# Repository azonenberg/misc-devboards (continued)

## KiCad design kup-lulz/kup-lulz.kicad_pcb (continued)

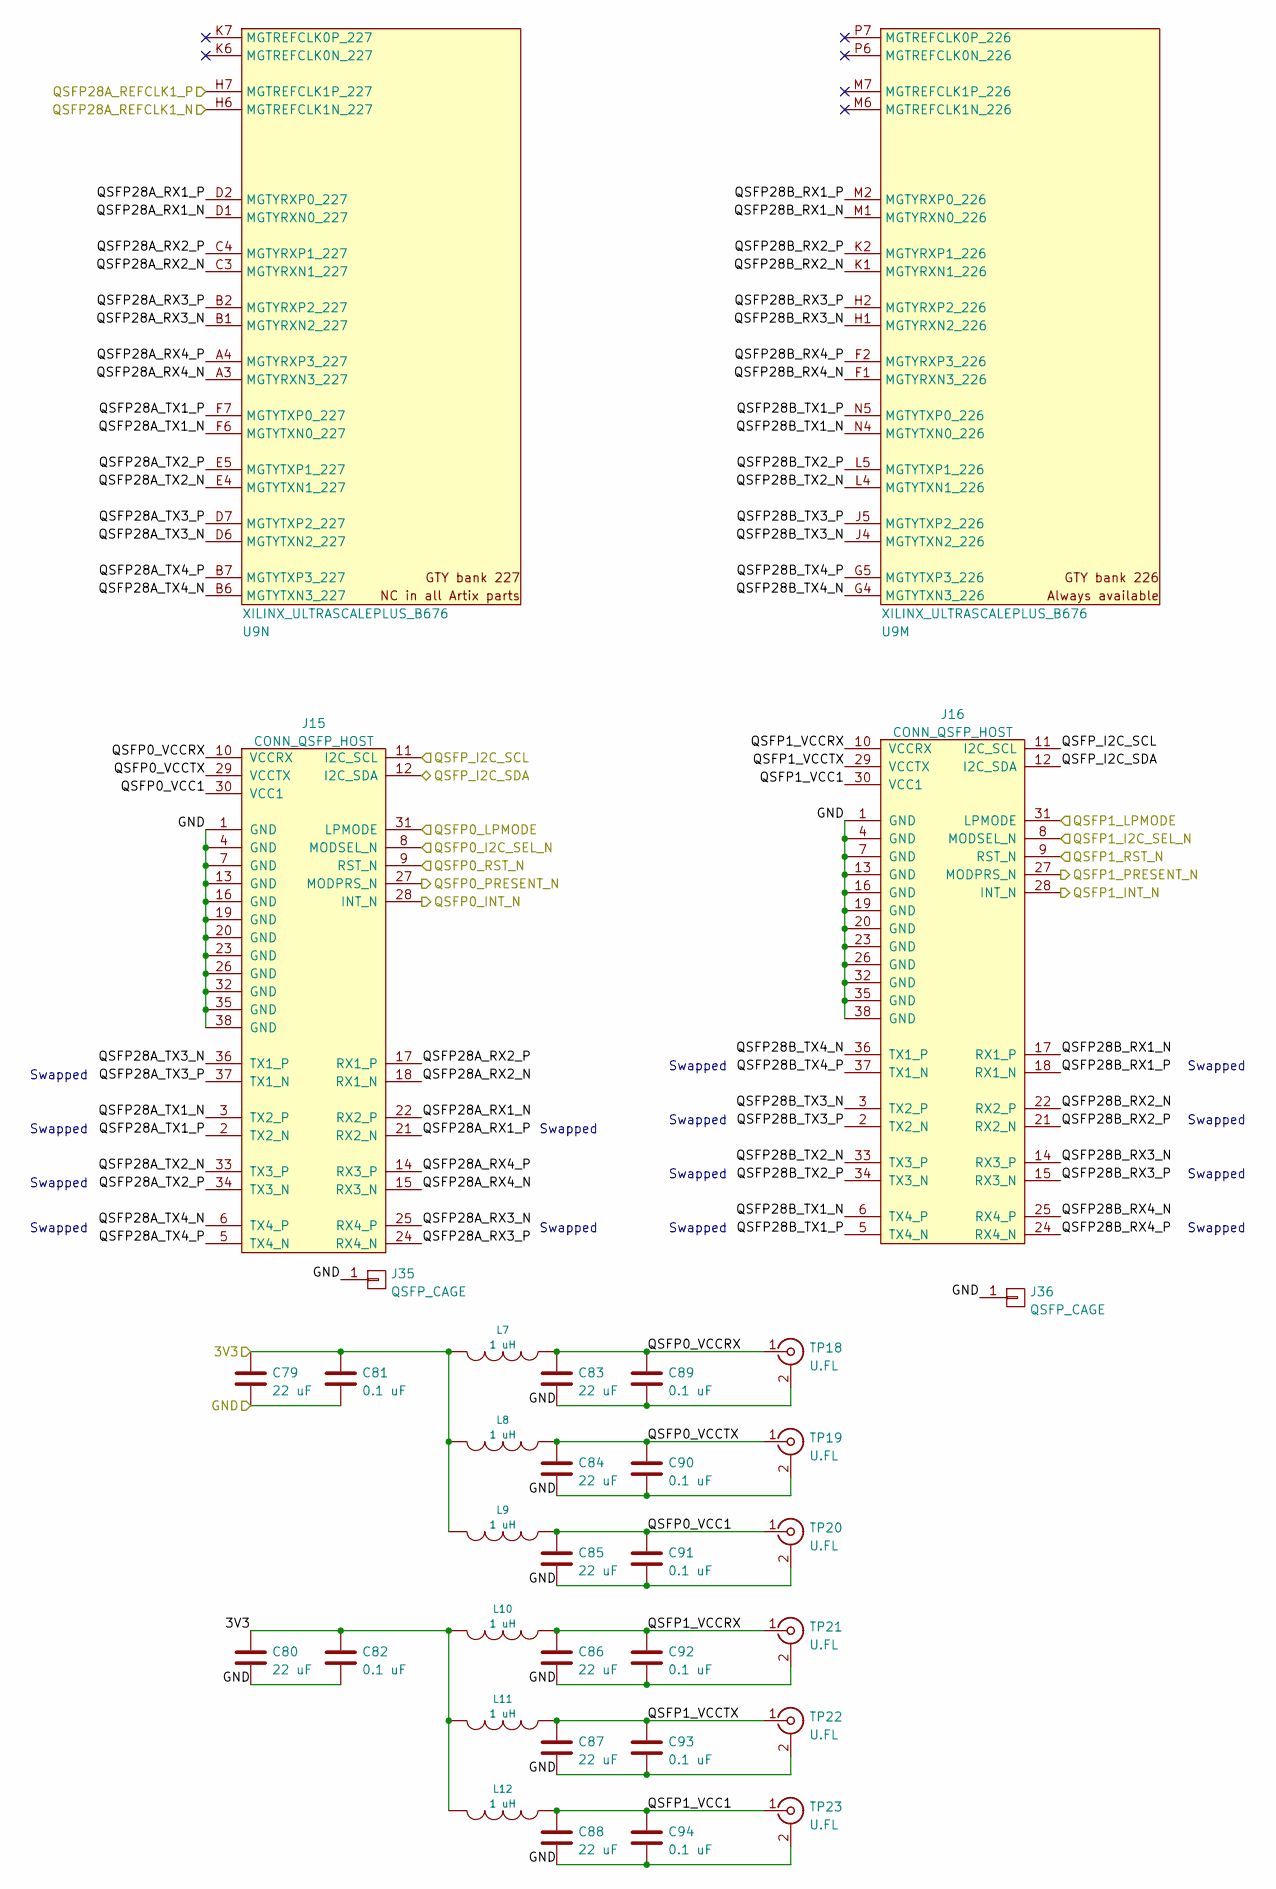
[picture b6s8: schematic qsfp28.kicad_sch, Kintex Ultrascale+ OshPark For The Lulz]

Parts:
C79, C80, C83, C84, C85, C86, C87, C88: 22 uF; EIA_1210_CAP_NOSILK
C81, C82, C89, C90, C91, C92, C93, C94: 0.1 uF; EIA_0402_CAP_NOSILK
J15, J16: CONN_QSFP_HOST; CONN_ZQSFP+_TE_1551920-2
J35, J36: QSFP_CAGE; CONN_ZQSFP+_CAGE_TE_4-2170705-5
L7, L8, L9, L10, L11, L12: 1 uH; EIA_0805_INDUCTOR_NOSILK
TP18, TP19, TP20, TP21, TP22, TP23: U.FL; CONN_U.FL_TE_1909763-1
U9: XILINX_ULTRASCALEPLUS_B676; BGA_676_27x27_FULLARRAY_1MM_FFG676

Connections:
/3V3: C79.1, C80.1, C81.1, C82.1, L7.2, L8.2, L9.2, L10.2, L11.2, L12.2; also elsewhere on the board
/GND: C79.2, C80.2, C81.2, C82.2, C83.2, C84.2, C85.2, C86.2, C87.2, C88.2, C89.2, C90.2, C91.2, C92.2, C93.2, C94.2, J15.1 (GND), J15.4 (GND), J15.7 (GND), J15.13 (GND), J15.16 (GND), J15.19 (GND), J15.20 (GND), J15.23 (GND), J15.26 (GND), J15.32 (GND), J15.35 (GND), J15.38 (GND), J16.1 (GND), J16.4 (GND), J16.7 (GND), J16.13 (GND), J16.16 (GND), J16.19 (GND), J16.20 (GND), J16.23 (GND), J16.26 (GND), J16.32 (GND), J16.35 (GND), J16.38 (GND), J35.1, J36.1, TP18.2 (Ext), TP19.2 (Ext), TP20.2 (Ext), TP21.2 (Ext), TP22.2 (Ext), TP23.2 (Ext); also elsewhere on the board
/Management/QSFP0_I2C_SEL_N: J15.8 (MODSEL_N); also elsewhere on the board
/Management/QSFP0_INT_N: J15.28 (INT_N); also elsewhere on the board
/Management/QSFP0_LPMODE: J15.31 (LPMODE); also elsewhere on the board
/Management/QSFP0_PRESENT_N: J15.27 (MODPRS_N); also elsewhere on the board
/Management/QSFP0_RST_N: J15.9 (RST_N); also elsewhere on the board
/Management/QSFP1_I2C_SEL_N: J16.8 (MODSEL_N); also elsewhere on the board
/Management/QSFP1_INT_N: J16.28 (INT_N); also elsewhere on the board
/Management/QSFP1_LPMODE: J16.31 (LPMODE); also elsewhere on the board
/Management/QSFP1_PRESENT_N: J16.27 (MODPRS_N); also elsewhere on the board
/Management/QSFP1_RST_N: J16.9 (RST_N); also elsewhere on the board
/Management/QSFP_I2C_SCL: J15.11 (I2C_SCL), J16.11 (I2C_SCL); also elsewhere on the board
/Management/QSFP_I2C_SDA: J15.12 (I2C_SDA), J16.12 (I2C_SDA); also elsewhere on the board
/QSFP28 interface/QSFP0_VCC1: C85.1, C91.1, J15.30 (VCC1), L9.1, TP20.1 (In)
/QSFP28 interface/QSFP0_VCCRX: C83.1, C89.1, J15.10 (VCCRX), L7.1, TP18.1 (In)
/QSFP28 interface/QSFP0_VCCTX: C84.1, C90.1, J15.29 (VCCTX), L8.1, TP19.1 (In)
/QSFP28 interface/QSFP1_VCC1: C88.1, C94.1, J16.30 (VCC1), L12.1, TP23.1 (In)
/QSFP28 interface/QSFP1_VCCRX: C86.1, C92.1, J16.10 (VCCRX), L10.1, TP21.1 (In)
/QSFP28 interface/QSFP1_VCCTX: C87.1, C93.1, J16.29 (VCCTX), L11.1, TP22.1 (In)
/QSFP28 interface/QSFP28A_RX1_N: J15.22 (RX2_P), U9.D1 (MGTYRXN0_227)
/QSFP28 interface/QSFP28A_RX1_P: J15.21 (RX2_N), U9.D2 (MGTYRXP0_227)
/QSFP28 interface/QSFP28A_RX2_N: J15.18 (RX1_N), U9.C3 (MGTYRXN1_227)
/QSFP28 interface/QSFP28A_RX2_P: J15.17 (RX1_P), U9.C4 (MGTYRXP1_227)
/QSFP28 interface/QSFP28A_RX3_N: J15.25 (RX4_P), U9.B1 (MGTYRXN2_227)
/QSFP28 interface/QSFP28A_RX3_P: J15.24 (RX4_N), U9.B2 (MGTYRXP2_227)
/QSFP28 interface/QSFP28A_RX4_N: J15.15 (RX3_N), U9.A3 (MGTYRXN3_227)
/QSFP28 interface/QSFP28A_RX4_P: J15.14 (RX3_P), U9.A4 (MGTYRXP3_227)
/QSFP28 interface/QSFP28A_TX1_N: J15.3 (TX2_P), U9.F6 (MGTYTXN0_227)
/QSFP28 interface/QSFP28A_TX1_P: J15.2 (TX2_N), U9.F7 (MGTYTXP0_227)
/QSFP28 interface/QSFP28A_TX2_N: J15.33 (TX3_P), U9.E4 (MGTYTXN1_227)
/QSFP28 interface/QSFP28A_TX2_P: J15.34 (TX3_N), U9.E5 (MGTYTXP1_227)
/QSFP28 interface/QSFP28A_TX3_N: J15.36 (TX1_P), U9.D6 (MGTYTXN2_227)
/QSFP28 interface/QSFP28A_TX3_P: J15.37 (TX1_N), U9.D7 (MGTYTXP2_227)
/QSFP28 interface/QSFP28A_TX4_N: J15.6 (TX4_P), U9.B6 (MGTYTXN3_227)
/QSFP28 interface/QSFP28A_TX4_P: J15.5 (TX4_N), U9.B7 (MGTYTXP3_227)
/QSFP28 interface/QSFP28B_RX1_N: J16.17 (RX1_P), U9.M1 (MGTYRXN0_226)
/QSFP28 interface/QSFP28B_RX1_P: J16.18 (RX1_N), U9.M2 (MGTYRXP0_226)
/QSFP28 interface/QSFP28B_RX2_N: J16.22 (RX2_P), U9.K1 (MGTYRXN1_226)
/QSFP28 interface/QSFP28B_RX2_P: J16.21 (RX2_N), U9.K2 (MGTYRXP1_226)
/QSFP28 interface/QSFP28B_RX3_N: J16.14 (RX3_P), U9.H1 (MGTYRXN2_226)
/QSFP28 interface/QSFP28B_RX3_P: J16.15 (RX3_N), U9.H2 (MGTYRXP2_226)
/QSFP28 interface/QSFP28B_RX4_N: J16.25 (RX4_P), U9.F1 (MGTYRXN3_226)
/QSFP28 interface/QSFP28B_RX4_P: J16.24 (RX4_N), U9.F2 (MGTYRXP3_226)
/QSFP28 interface/QSFP28B_TX1_N: J16.6 (TX4_P), U9.N4 (MGTYTXN0_226)
/QSFP28 interface/QSFP28B_TX1_P: J16.5 (TX4_N), U9.N5 (MGTYTXP0_226)
/QSFP28 interface/QSFP28B_TX2_N: J16.33 (TX3_P), U9.L4 (MGTYTXN1_226)
/QSFP28 interface/QSFP28B_TX2_P: J16.34 (TX3_N), U9.L5 (MGTYTXP1_226)
/QSFP28 interface/QSFP28B_TX3_N: J16.3 (TX2_P), U9.J4 (MGTYTXN2_226)
/QSFP28 interface/QSFP28B_TX3_P: J16.2 (TX2_N), U9.J5 (MGTYTXP2_226)
/QSFP28 interface/QSFP28B_TX4_N: J16.36 (TX1_P), U9.G4 (MGTYTXN3_226)
/QSFP28 interface/QSFP28B_TX4_P: J16.37 (TX1_N), U9.G5 (MGTYTXP3_226)
/REFCLK2_N: U9.H6 (MGTREFCLK1N_227); also elsewhere on the board
/REFCLK2_P: U9.H7 (MGTREFCLK1P_227); also elsewhere on the board

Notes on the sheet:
Swapped

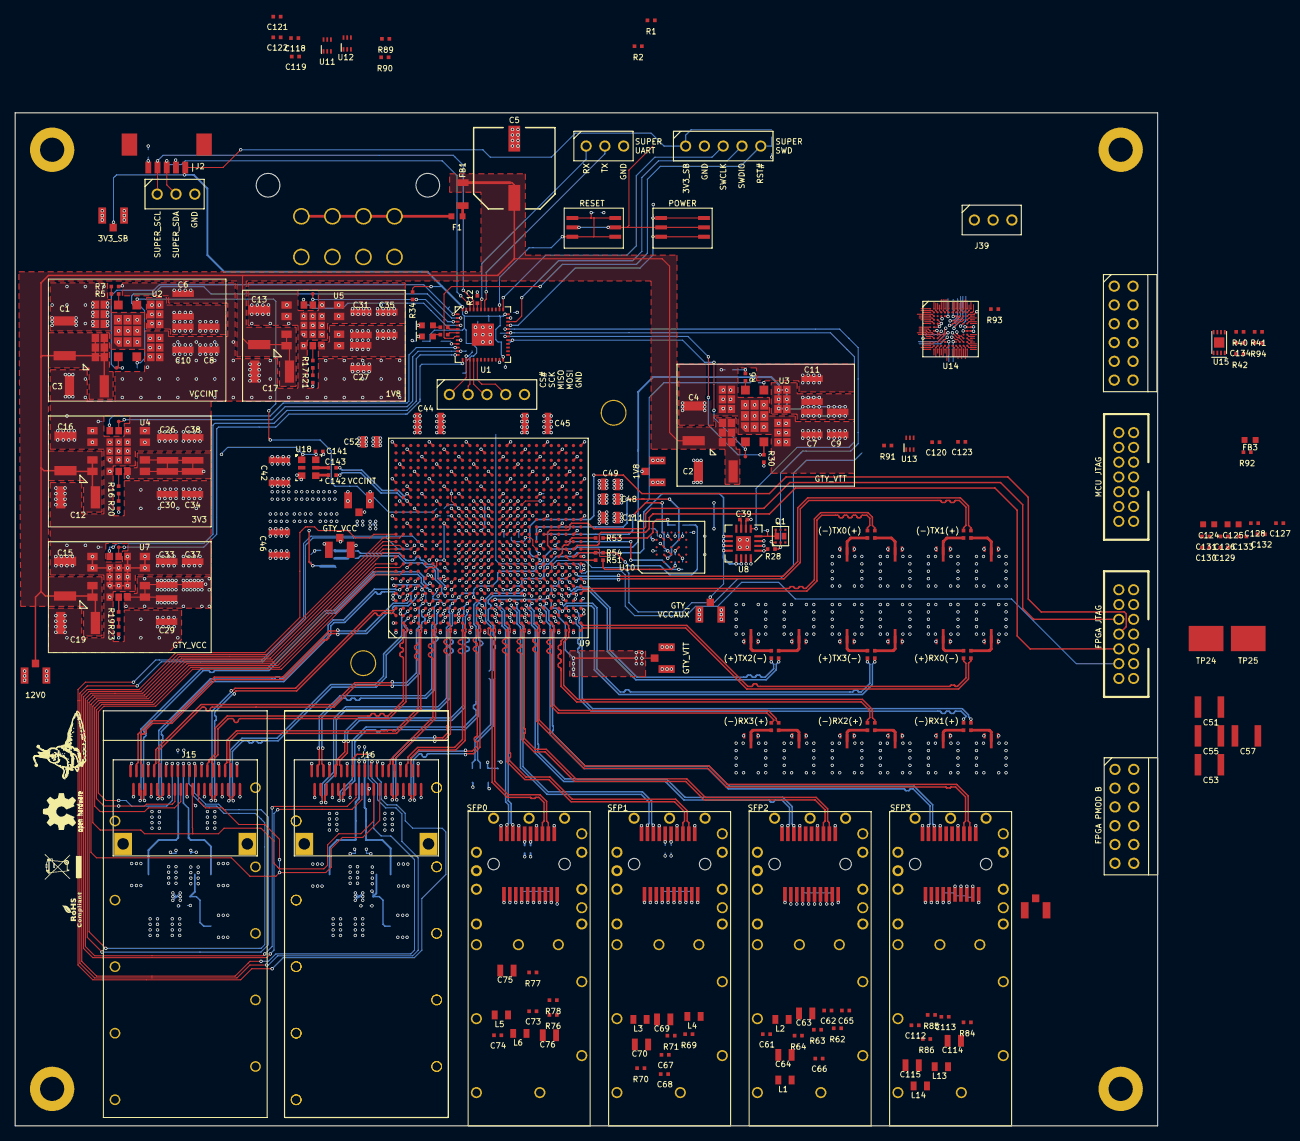
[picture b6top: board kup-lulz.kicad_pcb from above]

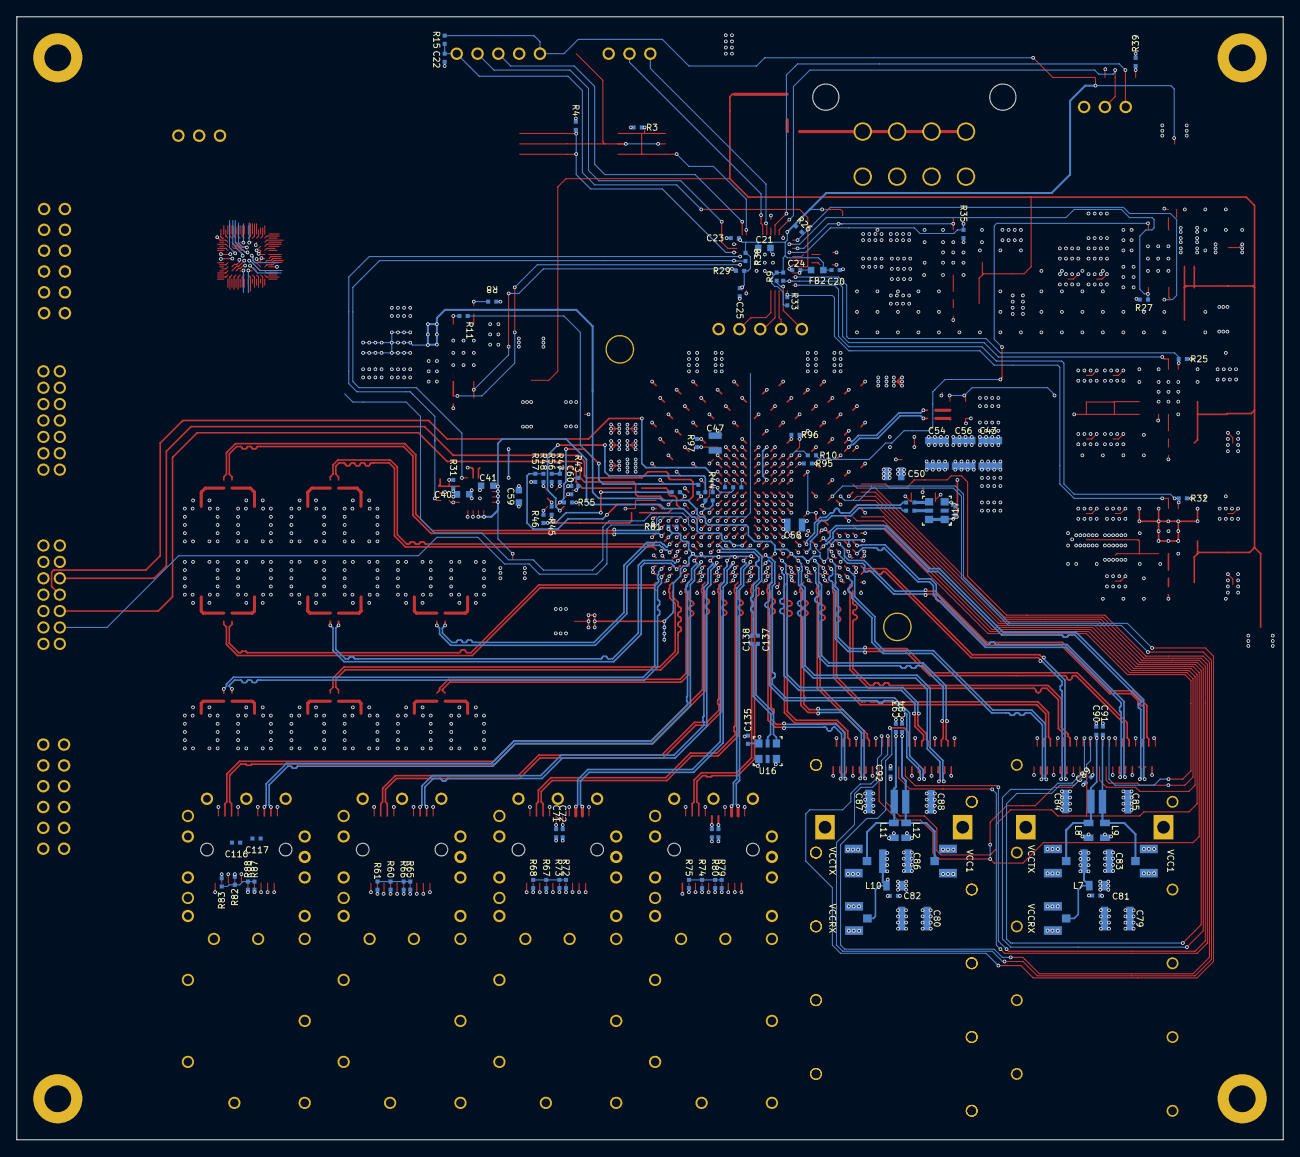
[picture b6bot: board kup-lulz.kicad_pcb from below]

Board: 4 copper layers, 154.5 x 137.0 mm, 340 parts (110 on the bottom side), 286 nets.

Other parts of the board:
J36#2: QSFP_CAGE; CONN_ZQSFP+_CAGE_TE_4-2170705-5

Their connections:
/GND: J36#2.1; also elsewhere on the board

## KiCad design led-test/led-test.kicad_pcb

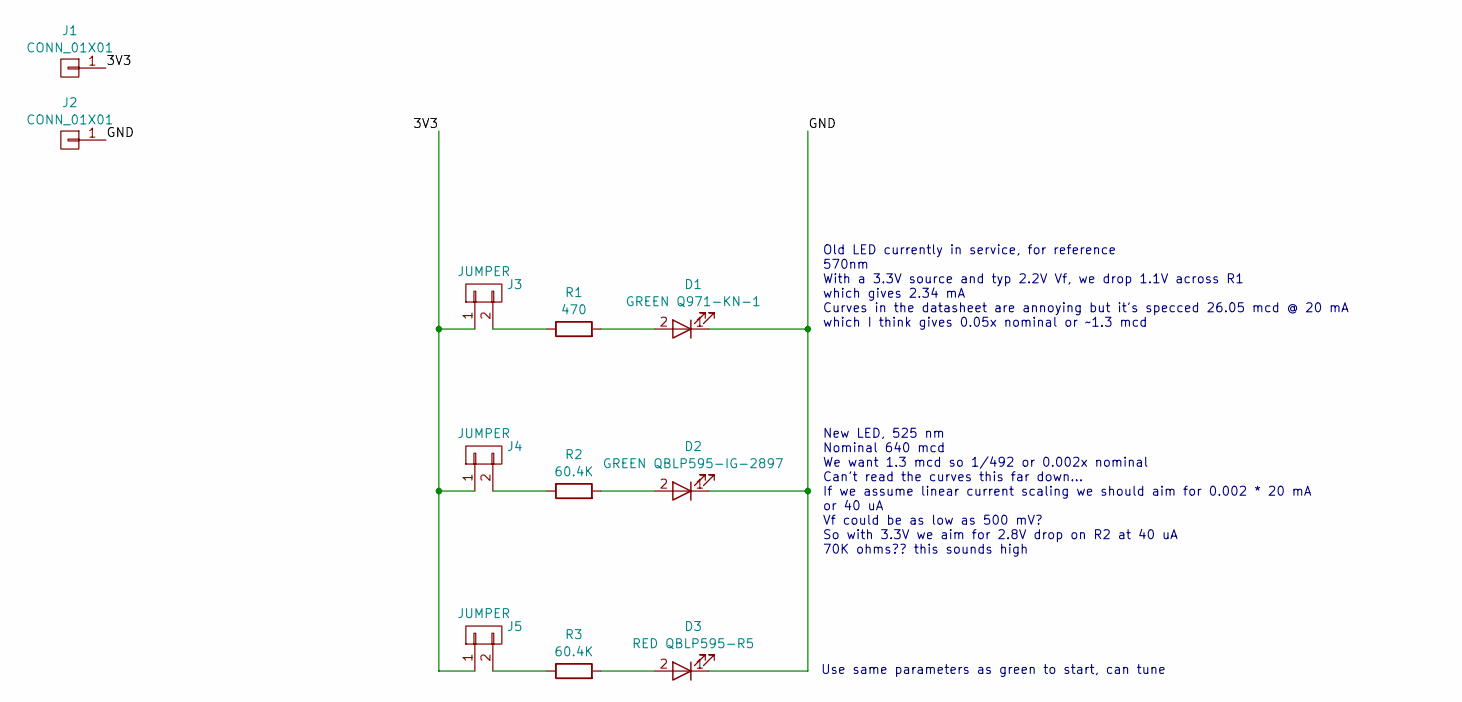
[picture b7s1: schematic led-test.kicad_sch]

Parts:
D1: GREEN Q971-KN-1; EIA_0603_LED
D2: GREEN QBLP595-IG-2897; EIA_0402_LED
D3: RED QBLP595-R5; EIA_0402_LED
J1, J2: CONN_01X01; TESTPOINT_SMT_KEYSTONE_5016
J3, J4, J5: JUMPER; CONN_HEADER_2.54MM_1x2
R1: 470; EIA_0402_RES_NOSILK
R2, R3: 60.4K; EIA_0402_RES_NOSILK

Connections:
/3V3: J1.1, J3.1, J4.1, J5.1
/GND: D1.1 (K), D2.1 (K), D3.1 (K), J2.1
unnamed: D1.2 (A), R1.2
unnamed: D2.2 (A), R2.2
unnamed: D3.2 (A), R3.2
unnamed: J3.2, R1.1
unnamed: J4.2, R2.1
unnamed: J5.2, R3.1

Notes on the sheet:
Old LED currently in service, for reference 570nm With a 3.3V source and typ 2.2V Vf, we drop 1.1V across R1 which gives 2.34 mA Curves in the datasheet are annoying but it's specced 26.05 mcd @ 20 mA which I think gives 0.05x nominal or ~1.3 mcd
New LED, 525 nm Nominal 640 mcd We want 1.3 mcd so 1/492 or 0.002x nominal Can't read the curves this far down... If we assume linear current scaling we should aim for 0.002 * 20 mA or 40 uA Vf could be as low as 500 mV? So with 3.3V we aim for 2.8V drop on R2 at 40 uA 70K ohms?? this sounds high
Use same parameters as green to start, can tune

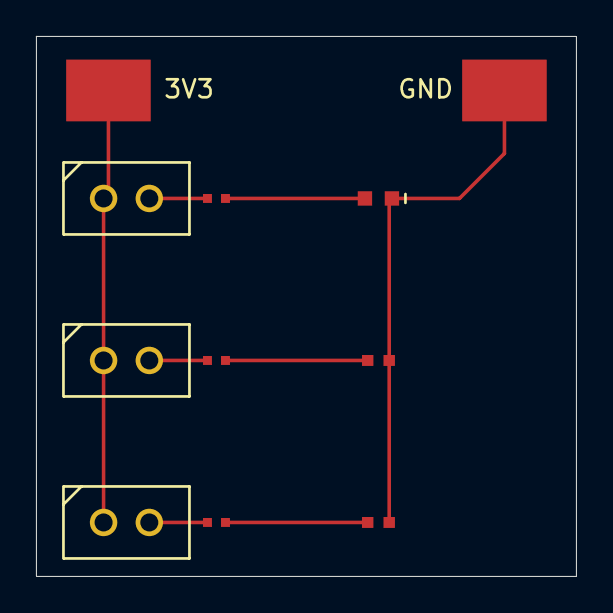
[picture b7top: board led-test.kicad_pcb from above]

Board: 2 copper layers, 30.0 x 30.0 mm, 11 parts (0 on the bottom side), 8 nets.

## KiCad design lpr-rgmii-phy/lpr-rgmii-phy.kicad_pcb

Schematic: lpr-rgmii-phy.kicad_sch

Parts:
C1, C4: 22 uF; EIA_1812_CAP_NOSILK
C2, C3, C5, C6: 22 uF; EIA_1210_CAP_NOSILK
C7, C17, C18, C23, C24, C25, C26, C27, C28, C29, C30, C31, C32, C33, C34, C35: 0.47 uF; EIA_0402_CAP_NOSILK
C8, C9, C10, C11, C12, C19, C20, C21, C22: 4.7 uF; EIA_0603_CAP_NOSILK
C13, C14, C15, C16: 0.1 uF; EIA_0402_CAP_NOSILK
FB1, FB2, FB3, FB4: MI0603J601R-10; EIA_0603_INDUCTOR_NOSILK
J1: LPR_HEADER; CONN_HEADER_2.0MM_2x20_SMT_MOLEX_0877594014
J2: 0826-1G1T-23-F; CONN_BELFUSE_0826_1G1T_23_F
M1: LOGO; LONGTHING-1200DPI
M2: LOGO; Logo_silk_OSHW_6x6mm
M3: LOGO; Logo_silk_ROHS_5x2.8mm
M4: LOGO; Logo_silk_WEEE_3.4x5mm
R1, R3, R4: 100K; EIA_0402_RES_NOSILK
R2: 22.1K; EIA_0402_RES_NOSILK
R5, R6: 470; EIA_0402_RES_NOSILK
R7, R9, R10, R11, R12, R13, R14: 33; EIA_0402_RES_NOSILK
R8, R16, R24: 1K; EIA_0402_RES_NOSILK
R15: 12.1K 1%; EIA_0402_RES_NOSILK
R17, R18, R19, R20, R21, R22, R23, R25, R26: 10K; EIA_0402_RES_NOSILK
TP1, TP2, TP3, TP4, TP5, TP6: U.FL; CONN_U.FL_TE_1909763-1
TP7, TP9: TESTPOINT; TESTPOINT_SMT_0.5MM
TP8: TESTCLIP; TESTPOINT_SMT_KEYSTONE_5016
U1, U2: MUN12AD03-SE; MODULE_CYNTEC_MUN12AD03-SE
U3: ECS-1612MV-250-CN; OSCILLATOR_1.6x1.2
U4: KSZ9031RN; QFN_48_0.5MM_7x7MM
U5, U6: RCLAMP0514M; SOP_10_0.5MM_3MM

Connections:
/1V2: C5.1, C6.1, C8.1, C11.1, FB1.1, FB3.1, FB4.1, R3.1, TP2.1 (In), U2.4 (VOUT), U2.5 (VOUT)
/1V2_FB: R3.2, R4.1, U2.6 (FB)
/1V2_PGOOD: R26.2, TP7.1, U2.7 (PGOOD)
/3V3: C2.1, C3.1, C7.1, C9.1, C10.1, C17.1, C23.1, C28.1, FB2.1, R1.1, R5.1, R6.1, R17.1, R18.1, R19.1, R20.1, R24.1, TP1.1 (In), U1.4 (VOUT), U1.5 (VOUT), U3.1 (E/D#), U3.4 (Vdd), U4.16 (DVDDH), U4.34 (DVDDH), U4.40 (DVDDH)
/3V3_FB: R1.2, R2.1, U1.6 (FB)
/3V3_PGOOD: R25.2, TP9.1, U1.7 (PGOOD)
/5V5: C1.1, C4.1, J1.35 (5.5V), J1.36 (5.5V), J1.37 (5.5V), J1.38 (5.5V), R25.1, R26.1, U1.1 (EN), U1.2 (VIN), U2.1 (EN), U2.2 (VIN)
/A1V2: C21.1, C25.1, C31.1, FB3.2, TP5.1 (In), U4.4 (AVDDL), U4.9 (AVDDL)
/A1V2_PLL: C22.1, C26.1, FB4.2, TP4.1 (In), U4.44 (AVDDL_PLL)
/A3V3: C20.1, C27.1, C30.1, C33.1, FB2.2, TP6.1 (In), U4.1 (AVDDH), U4.12 (AVDDH), U4.47 (NC/AVDDH), U5.3 (Vcc), U6.3 (Vcc)
/D1V2: C12.1, C18.1, C19.1, C24.1, C29.1, C32.1, C34.1, C35.1, FB1.2, TP3.1 (In), U4.14 (DVDDL), U4.18 (DVDDL), U4.23 (DVDDL), U4.26 (DVDDL), U4.30 (DVDDL), U4.39 (DVDDL)
/ETH_A_N: J2.10 (CH1_N), U4.3 (TXRXM_A), U5.4 (LINE_3), U5.7 (NC_3)
/ETH_A_P: J2.11 (CH1_P), U4.2 (TXRXP_A), U5.5 (NC_4), U5.6 (LINE_4)
/ETH_B_N: J2.4 (CH2_P), U4.6 (TXRXM_B), U5.1 (LINE_1), U5.10 (NC_1)
/ETH_B_P: J2.5 (CH2_N), U4.5 (TXRXP_B), U5.2 (NC_2), U5.9 (LINE_2)
/ETH_CLK_25MHZ: R7.1, U4.46 (XI)
/ETH_C_N: J2.2 (CH3_N), U4.8 (TXRXM_C), U6.4 (LINE_3), U6.7 (NC_3)
/ETH_C_P: J2.3 (CH3_P), U4.7 (TXRXP_C), U6.5 (NC_4), U6.6 (LINE_4)
/ETH_D_N: J2.8 (CH4_P), U4.11 (TXRXM_D), U6.1 (LINE_1), U6.10 (NC_1)
/ETH_D_P: J2.9 (CH4_N), U4.10 (TXRXP_D), U6.2 (NC_2), U6.9 (LINE_2)
/ETH_LED1_N: J2.13 (LED1_N), R16.2, U4.17 (LED1/PHYAD0)
/ETH_LED2_N: J2.15 (LED2_N), R8.2, U4.15 (LED2/PHYAD1)
/ETH_MDC: J1.24 (RFE_GPIO3), U4.36 (MDC)
/ETH_MDIO: J1.23 (RFE_GPIO12), R24.2, U4.37 (MDIO)
/ETH_RST_N: J1.19 (RFE_GPIO14), U4.42 (RESET_N)
/ETH_RXD0: J1.6 (RFE_GPIO7), R12.1, R21.2
/ETH_RXD1: J1.5 (RFE_GPIO16), R11.1, R20.2
/ETH_RXD2: J1.8 (RFE_GPIO6), R10.1, R19.2
/ETH_RXD3: J1.7 (RFE_GPIO15), R9.1, R18.2
/ETH_RX_CLK: J1.4 (RFE_GPIO8_CC), R14.1, R23.2
/ETH_RX_DV: J1.3 (RFE_GPIO17), R13.1, R22.2
/GND: C1.2, C2.2, C3.2, C4.2, C5.2, C6.2, C7.2, C8.2, C9.2, C10.2, C11.2, C12.2, C13.1, C14.1, C15.1, C16.1, C17.2, C18.2, C19.2, C20.2, C21.2, C22.2, C23.2, C24.2, C25.2, C26.2, C27.2, C28.2, C29.2, C30.2, C31.2, C32.2, C33.2, C34.2, C35.2, J1.1 (GND), J1.2 (GND), J1.9 (GND), J1.10 (GND), J1.17 (GND), J1.18 (GND), J1.29 (GND), J1.30 (GND), J1.33 (GND), J1.34 (GND), J1.39 (GND), J1.40 (GND), J2.17 (SHLD), R2.2, R4.2, R8.1, R15.1, R16.1, R21.1, R22.1, R23.1, TP1.2 (Ext), TP2.2 (Ext), TP3.2 (Ext), TP4.2 (Ext), TP5.2 (Ext), TP6.2 (Ext), TP8.1, U1.3 (GND), U1.PAD (GND), U2.3 (GND), U2.PAD (GND), U3.2 (Vss), U4.13 (NC/GND), U4.29 (VSS), U4.PAD, U5.8 (Gnd), U6.8 (Gnd)
/RGMII_TXD0: J1.31 (RFE_GPIO9), U4.19 (TXD0)
/RGMII_TXD1: J1.32 (RFE_GPIO0), U4.20 (TXD1)
/RGMII_TXD2: J1.27 (RFE_GPIO10), U4.21 (TXD2)
/RGMII_TXD3: J1.28 (RFE_GPIO1), U4.22 (TXD3)
/RGMII_TX_CLK: J1.25 (RFE_GPIO11), U4.24 (GTX_CLK)
/RGMII_TX_EN: J1.26 (RFE_GPIO2), U4.25 (TX_EN)
unnamed: C13.2, J2.12 (CH1_TAP)
unnamed: C14.2, J2.6 (CH2_TAP)
unnamed: C15.2, J2.1 (CH3_TAP)
unnamed: C16.2, J2.7 (CH4_TAP)
unnamed: J2.14 (LED1_P), R5.2
unnamed: J2.16 (LED2_P), R6.2
unnamed: R7.2, U3.3 (CLK)
unnamed: R17.2, U4.41 (CLK125_NDO/LED_MODE)
unnamed: R15.2, U4.48 (ISET)
unnamed: R12.2, U4.32 (RXD0/MODE0)
unnamed: R11.2, U4.31 (RXD1/MODE1)
unnamed: R10.2, U4.28 (RXD2/MODE2)
unnamed: R9.2, U4.27 (RXD3/MODE3)
unnamed: R14.2, U4.35 (RX_CLK/PHYAD2)
unnamed: R13.2, U4.33 (RX_DV/CLK125_EN)

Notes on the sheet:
Polarity swap KSZ9031 auto corrects
Strap: Disable CLK125_NDO we don't use
Vout = 0.6 * (1 + RfbT / RfbB) 1.2 = 0.6 * (1 + Rtop / Rbot) Rtop/Rbot = 1 Datasheet suggests 124K / 124K We can do 100k / 100k with what we have in stock
Strap: dual LEDs
Strap: PHYADR[1:0] = 2'b00
Strap: PHYADDR[2] = 0
Strap: advertise everything but gig/half
Vout = 0.6 * (1 + RfbT / RfbB) 3.3 = 0.6 * (1 + Rtop / Rbot) Rtop/Rbot = 4.5 Datasheet suggests 124K / 27.4K We can do 100k / 22.1k with what we have in stock

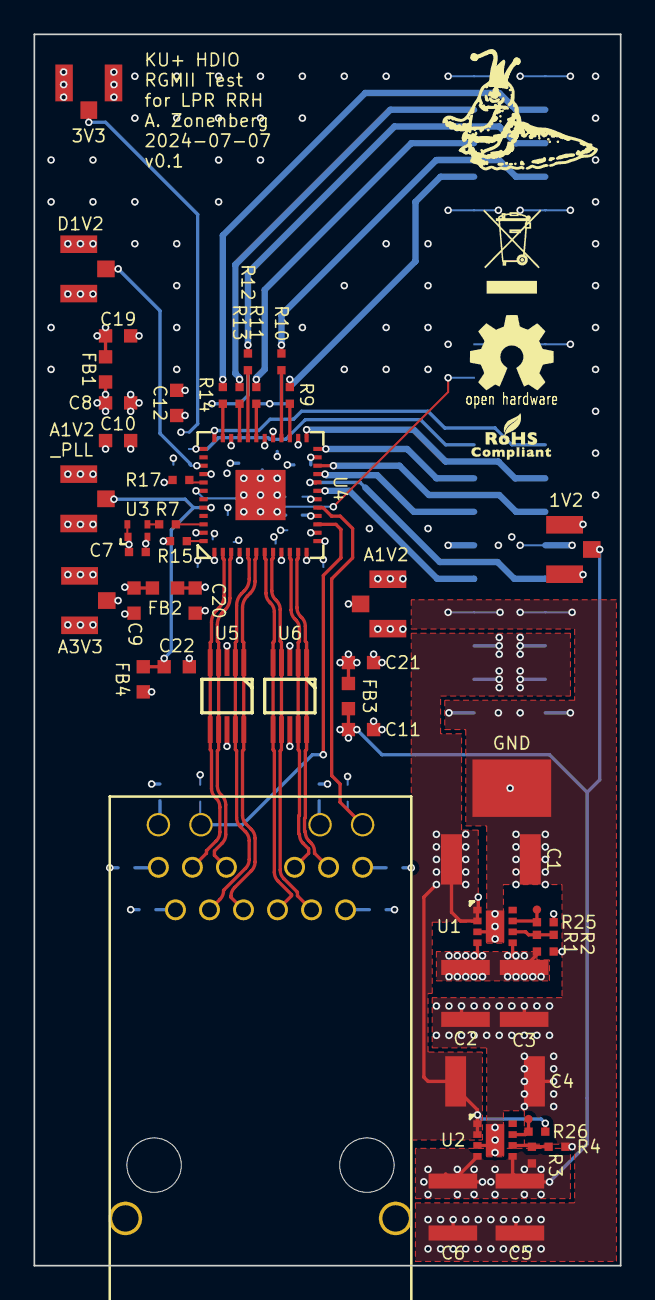
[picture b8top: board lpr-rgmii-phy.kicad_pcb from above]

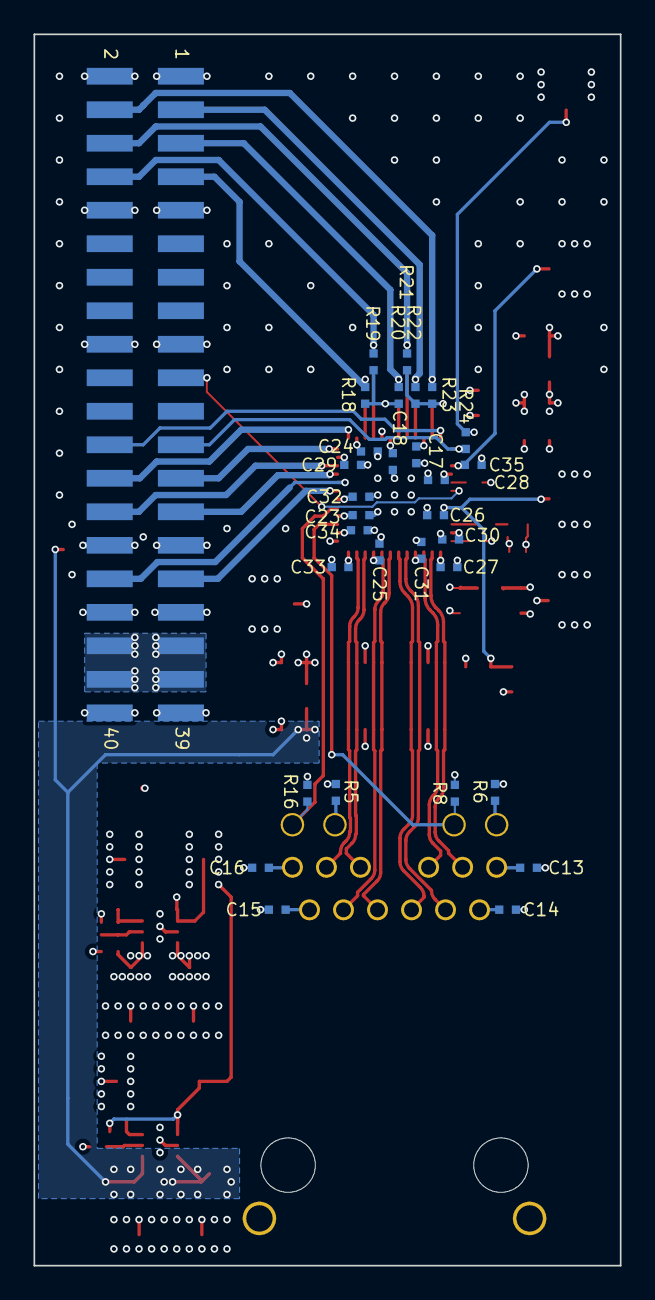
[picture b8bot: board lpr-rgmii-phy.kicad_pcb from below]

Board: 4 copper layers, 35.0 x 73.5 mm, 86 parts (31 on the bottom side), 53 nets.
